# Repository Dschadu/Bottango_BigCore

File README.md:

# ESP32 Bottango Control Board

This custom PCB is designed to serve as a **control and interface board** for projects using the [Bottango](https://www.bottango.com/) motion and animation control firmware.  
It provides robust connectivity, servo control, and expandability for animatronics or motion-based systems.

**Note**: This is a community project and not designed / maintained / officially supported by Bottango.

---

## Features

### Core
- **ESP32 microcontroller**
- **USB-C** connector for power and programming  
- **Selectable power source** for the ESP32:  
  - USB-C  
  - 5 V rail (from WS2812B)

---

### Inputs
- **4 user buttons** — freely assignable, e.g., for selecting animations  
- **1 stop button** — emergency or animation stop  
- **Potentiometer input** — for audio volume control  

---

### Outputs & Indicators
- **4 status LEDs** — indicate board or animation states  
- **Line-out audio output**  
- **6 servo connectors** (powered by dedicated power input)  
- **WS2812B output** — supports addressable RGB LEDs  
- **Selectable power source for audio section:**  
  - USB-C  
  - 5 V rail (from WS2812B)  
- **LED power indicators** for:  
  - 5 V  
  - 6 V  
  - USB-C  
  - 3.3 V  

---

### Connectivity
- **I²C (Qwiic-compatible connector)** — for sensor or peripheral expansion  
- **RS485 interface** — for robust long-distance serial communication  

---

## Power Overview

| Function             | Voltage  | Source Options               |
|----------------------|----------|------------------------------|
| ESP32                | 5 V      | USB-C / 5 V line             |
| Audio Output Circuit | 5 V      | USB-C / 5 V line             |
| WS2812B LEDs         | 5 V      | External supply              |
| Servos               | 6 V      | External supply              |

---

## Firmware Compatibility

This board is designed for use with **Bottango firmware**, providing smooth integration with Bottango Studio for real-time motion and animation control.  
Learn more at: [https://www.bottango.com/](https://www.bottango.com/)

**Note**: This is a community project and not designed / maintained / officially supported by Bottango.

---

## License

This hardware design is released under the  
**CERN Open Hardware Licence Version 2 – Weakly Reciprocal (CERN-OHL-W)**.  
© 2025 Martin Klein 

You are free to:
- Use, study, modify, and manufacture this design  
- Distribute modified versions under the same license  
- Incorporate this board into larger, closed-source systems, **as long as modifications to this board itself remain open-source**

For more information, see the [LICENSE](./LICENSE) file or the full text at
[CERN-OHL-W](https://gitlab.com/ohwr/project/cernohl/-/wikis/uploads/82b567f43ce515395f7ddbfbad7a8806/cern_ohl_w_v2.txt)

## Copyright Notice

Copyright Martin Klein 2025.

This source describes Open Hardware and is licensed under the CERN-OHLW v2

You may redistribute and modify this PCB and make products
using it under the terms of the CERN-OHL-W v2 (https:/cern.ch/cern-ohl).
This PCB is distributed WITHOUT ANY EXPRESS OR IMPLIED
WARRANTY, INCLUDING OF MERCHANTABILITY, SATISFACTORY QUALITY
AND FITNESS FOR A PARTICULAR PURPOSE. Please see the CERN-OHL-W v2
for applicable conditions.

Source location: https://github.com/Dschadu/Geistwerk-BigCore

As per CERN-OHL-W v2 section 4.1, should You produce hardware based on
these sources, You must maintain the Source Location visible in its
documentation.

## Acknowledgments

Special thanks to the Bottango team for providing an intuitive open platform for animatronic motion control.

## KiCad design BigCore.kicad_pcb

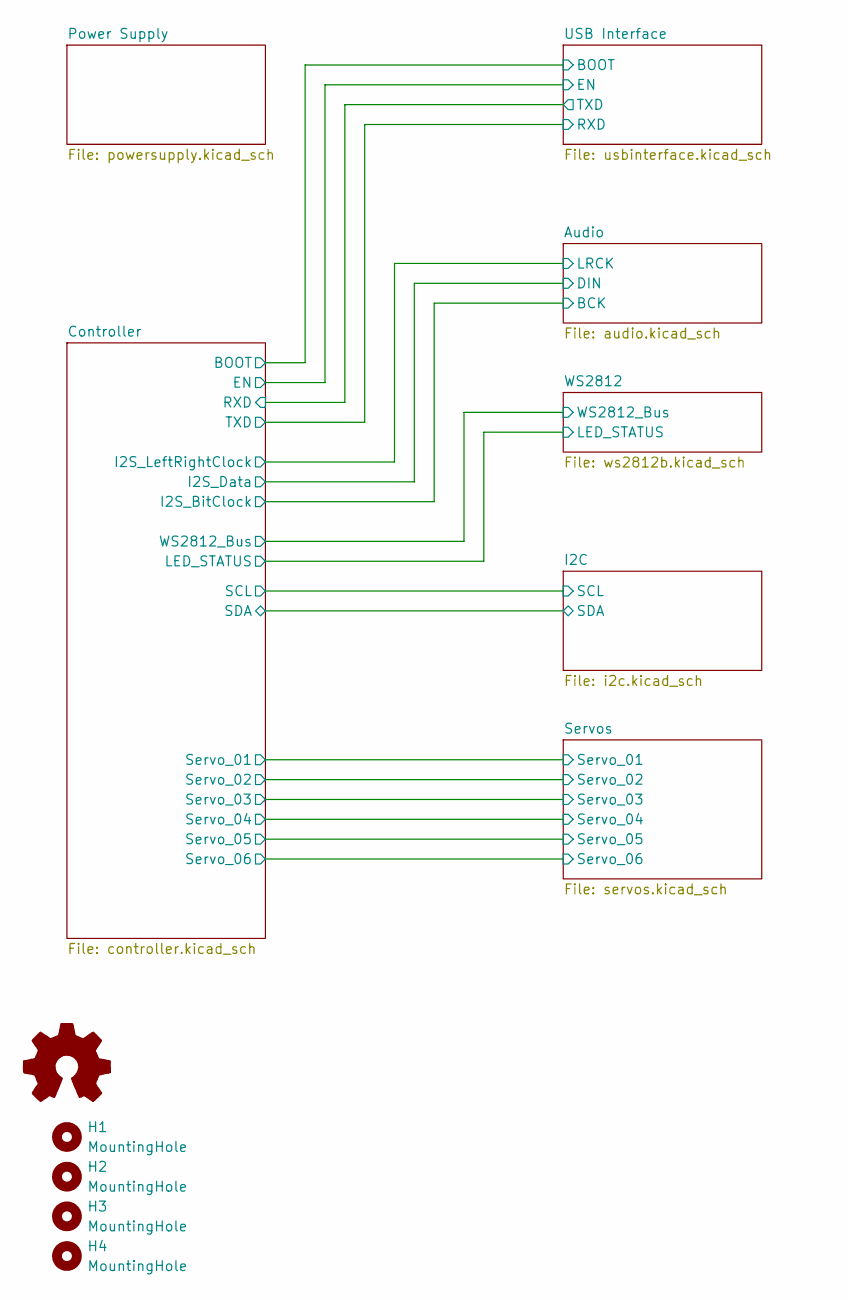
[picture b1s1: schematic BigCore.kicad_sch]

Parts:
H1, H2, H3, H4: MountingHole; MountingHole_3.2mm_M3
H5: Logo_Open_Hardware_Small; OSHW-Logo_5.7x6mm_SilkScreen

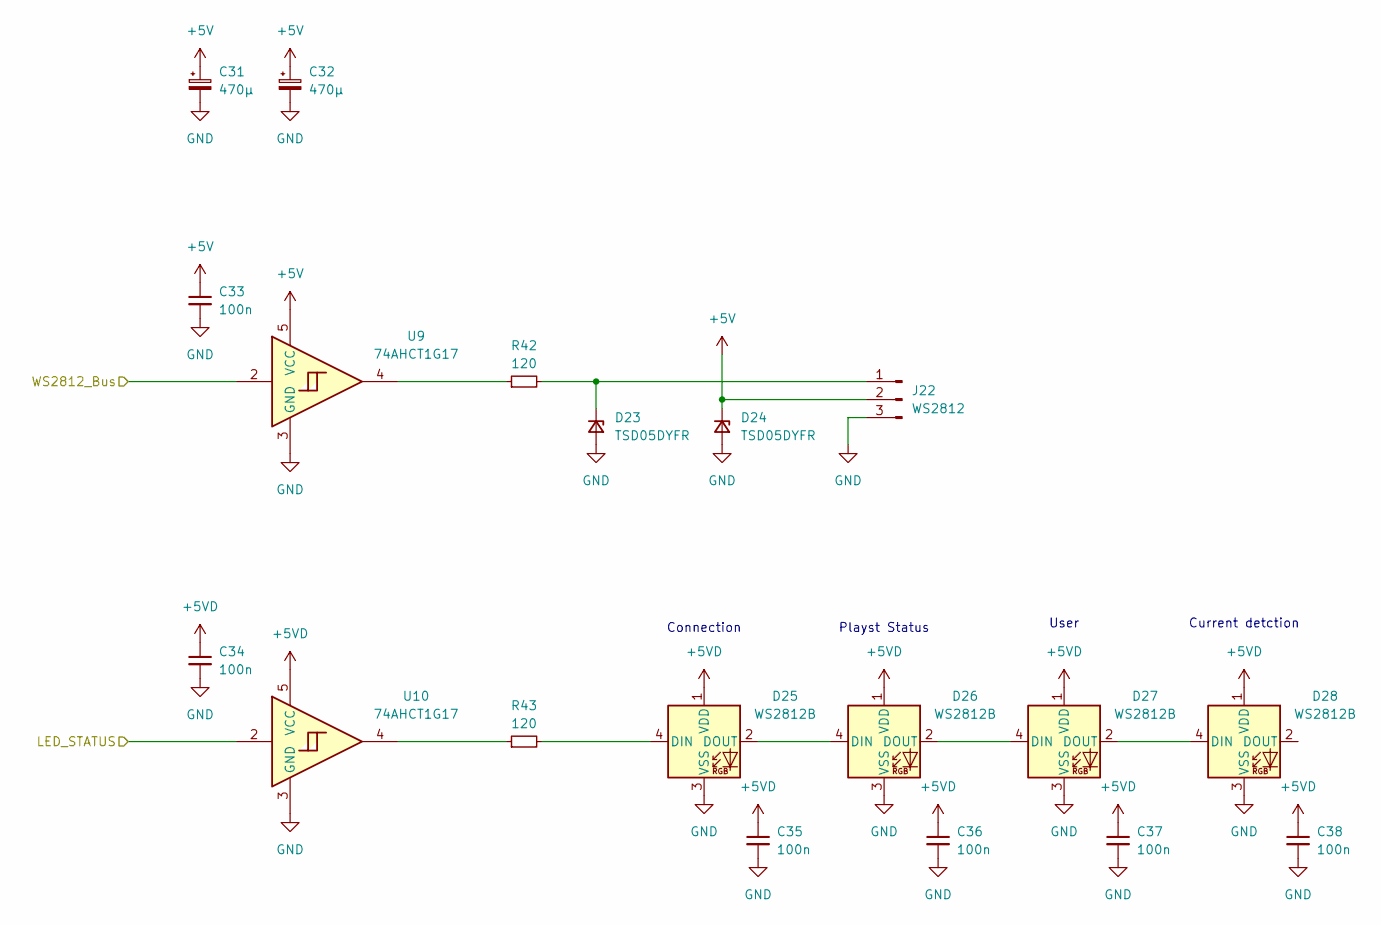
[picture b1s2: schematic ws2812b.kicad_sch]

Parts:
C31, C32: 470µ; CP_Radial_D8.0mm_P3.50mm
C33, C34, C35, C36, C37, C38: 100n; C_0603_1608Metric
D23, D24: TSD05DYFR; D_SOD-323_HandSoldering
D25, D26, D27, D28: WS2812B; LED_WS2812B-2020_PLCC4_2.0x2.0mm
J22: WS2812; JST_XH_B3B-XH-A_1x03_P2.50mm_Vertical
R42, R43: 120; R_0603_1608Metric
U9, U10: 74AHCT1G17; SOT-353_SC-70-5

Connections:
+5V: C31.1, C32.1, C33.1, D24.1 (K), J22.2, U9.5 (VCC); also elsewhere on the board
+5VD: C34.1, C35.1, C36.1, C37.1, C38.1, D25.1 (VDD), D26.1 (VDD), D27.1 (VDD), D28.1 (VDD), U10.5 (VCC); also elsewhere on the board
/Controller/LED_STATUS: U10.2; also elsewhere on the board
/Controller/WS2812_Bus: U9.2; also elsewhere on the board
GND: C31.2, C32.2, C33.2, C34.2, C35.2, C36.2, C37.2, C38.2, D23.2 (A), D24.2 (A), D25.3 (VSS), D26.3 (VSS), D27.3 (VSS), D28.3 (VSS), J22.3, U9.3 (GND), U10.3 (GND); also elsewhere on the board
unnamed: D23.1 (K), J22.1, R42.2
unnamed: D25.4 (DIN), R43.2
unnamed: D25.2 (DOUT), D26.4 (DIN)
unnamed: D26.2 (DOUT), D27.4 (DIN)
unnamed: D27.2 (DOUT), D28.4 (DIN)
unnamed: R42.1, U9.4
unnamed: R43.1, U10.4

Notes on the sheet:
Current detction
User
Connection
Playst Status

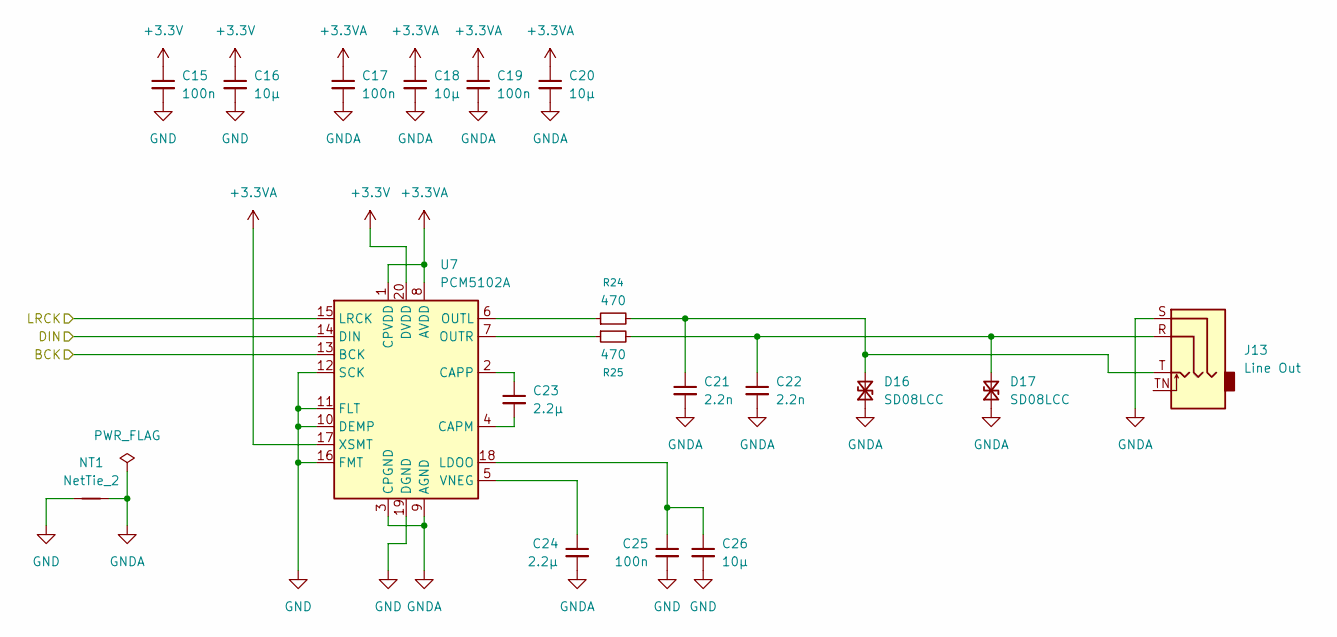
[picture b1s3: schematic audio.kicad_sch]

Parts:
C15, C17, C19, C25: 100n; C_0603_1608Metric
C16, C18, C20, C26: 10µ; C_0603_1608Metric
C21, C22: 2.2n; C_0603_1608Metric
C23, C24: 2.2µ; C_0603_1608Metric
D16, D17: SD08LCC; D_SOD-323_HandSoldering
J13: Line Out; Jack_3.5mm_CUI_SJ1-3524N_Horizontal
NT1: NetTie_2; NetTie-2_SMD_Pad0.5mm
R24, R25: 470; R_0603_1608Metric
U7: PCM5102A; TSSOP-20_4.4x6.5mm_P0.65mm

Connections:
+3.3V: C15.1, C16.1, U7.20 (DVDD); also elsewhere on the board
+3.3VA: C17.1, C18.1, C19.1, C20.1, U7.1 (CPVDD), U7.8 (AVDD), U7.17 (XSMT); also elsewhere on the board
/Controller/I2S_BitClock: U7.13 (BCK); also elsewhere on the board
/Controller/I2S_Data: U7.14 (DIN); also elsewhere on the board
/Controller/I2S_LeftRightClock: U7.15 (LRCK); also elsewhere on the board
GND: C15.2, C16.2, C25.2, C26.2, NT1.1, U7.10 (DEMP), U7.11 (FLT), U7.12 (SCK), U7.16 (FMT), U7.19 (DGND); also elsewhere on the board
GNDA: C17.2, C18.2, C19.2, C20.2, C21.2, C22.2, C24.2, D16.1 (A1), D17.1 (A1), J13.S, NT1.2, U7.3 (CPGND), U7.9 (AGND); also elsewhere on the board
unnamed: C21.1, D16.2 (A2), J13.T, R24.2
unnamed: C22.1, D17.2 (A2), J13.R, R25.2
unnamed: C23.2, U7.4 (CAPM)
unnamed: C23.1, U7.2 (CAPP)
unnamed: C25.1, C26.1, U7.18 (LDOO)
unnamed: R24.1, U7.6 (OUTL)
unnamed: R25.1, U7.7 (OUTR)
unnamed: C24.1, U7.5 (VNEG)

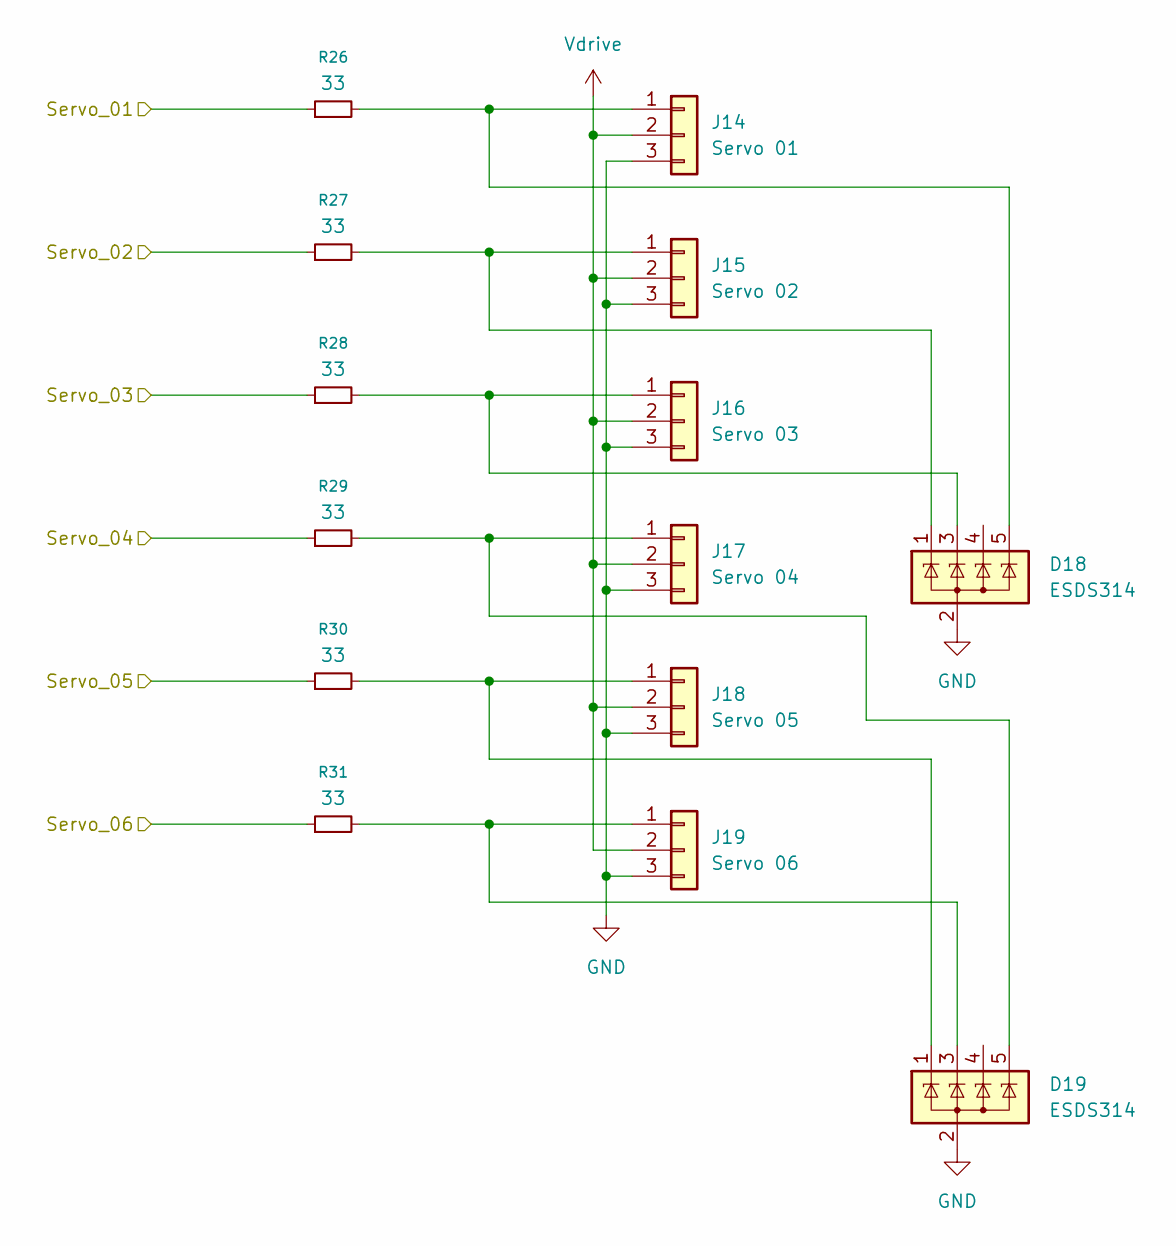
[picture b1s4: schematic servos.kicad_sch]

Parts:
D18, D19: ESDS314; SOT-23-5
J14: Servo 01; PinHeader_1x03_P2.54mm_Vertical
J15: Servo 02; PinHeader_1x03_P2.54mm_Vertical
J16: Servo 03; PinHeader_1x03_P2.54mm_Vertical
J17: Servo 04; PinHeader_1x03_P2.54mm_Vertical
J18: Servo 05; PinHeader_1x03_P2.54mm_Vertical
J19: Servo 06; PinHeader_1x03_P2.54mm_Vertical
R26, R27, R28, R29, R30, R31: 33; R_0603_1608Metric

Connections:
/Controller/Servo_01: R26.1; also elsewhere on the board
/Controller/Servo_02: R27.1; also elsewhere on the board
/Controller/Servo_03: R28.1; also elsewhere on the board
/Controller/Servo_04: R29.1; also elsewhere on the board
/Controller/Servo_05: R30.1; also elsewhere on the board
/Controller/Servo_06: R31.1; also elsewhere on the board
GND: D18.2 (A), D19.2 (A), J14.3, J15.3, J16.3, J17.3, J18.3, J19.3; also elsewhere on the board
unnamed: D18.5 (K), J14.1, R26.2
unnamed: D18.1 (K), J15.1, R27.2
unnamed: D18.3 (K), J16.1, R28.2
unnamed: D19.5 (K), J17.1, R29.2
unnamed: D19.1 (K), J18.1, R30.2
unnamed: D19.3 (K), J19.1, R31.2
Vdrive: J14.2, J15.2, J16.2, J17.2, J18.2, J19.2; also elsewhere on the board

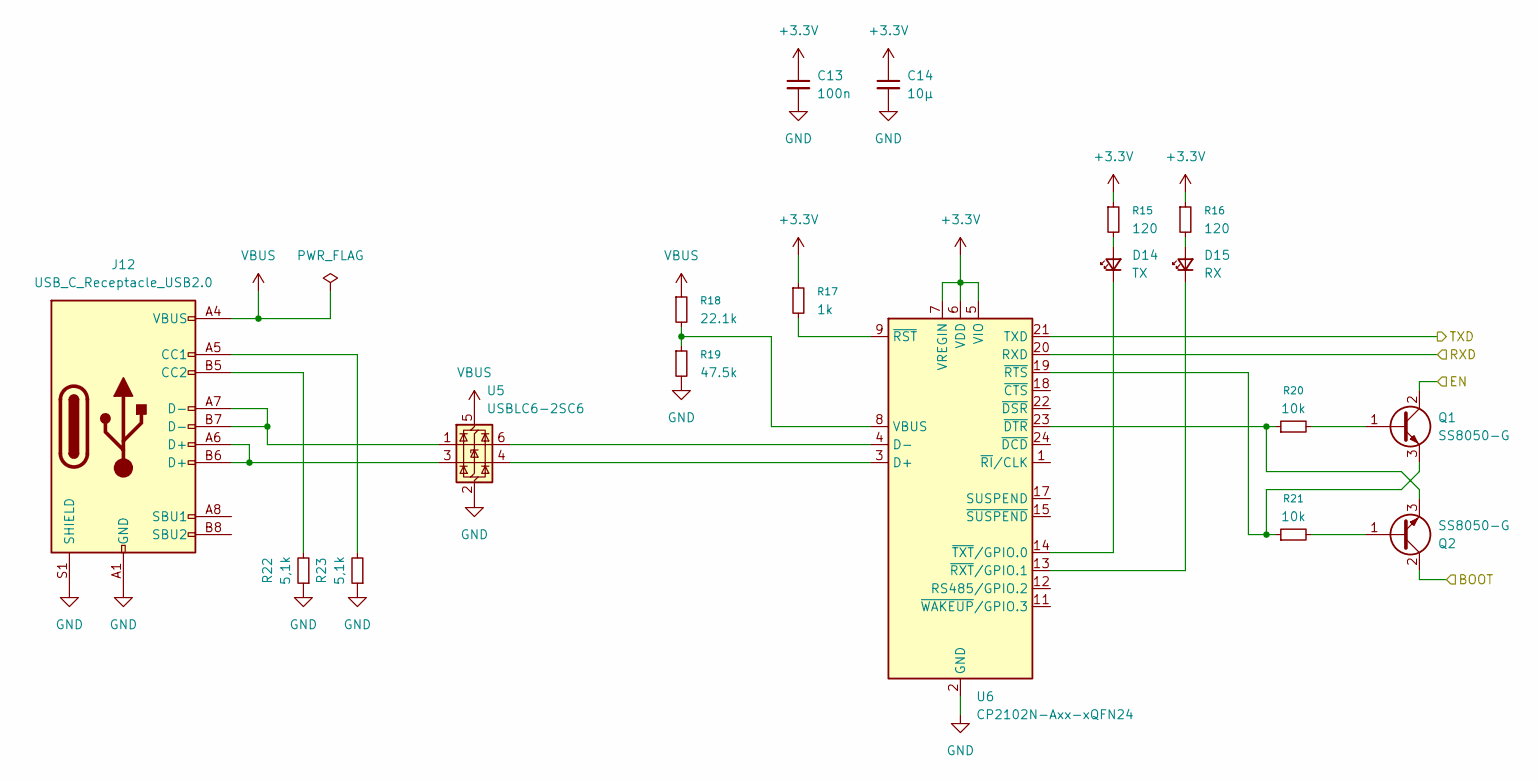
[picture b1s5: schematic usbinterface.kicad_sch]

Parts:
C13: 100n; C_0603_1608Metric
C14: 10µ; C_0603_1608Metric
D14: TX; LED_0805_2012Metric
D15: RX; LED_0805_2012Metric
J12: USB_C_Receptacle_USB2.0; USB_C_Receptacle_GCT_USB4105-xx-A_16P_TopMnt_Horizontal
Q1, Q2: SS8050-G; SOT-23-3
R15, R16: 120; R_0603_1608Metric
R17: 1k; R_0603_1608Metric
R18: 22.1k; R_0603_1608Metric
R19: 47.5k; R_0603_1608Metric
R20, R21: 10k; R_0603_1608Metric
R22, R23: 5,1k; R_0603_1608Metric
U5: USBLC6-2SC6; SOT-23-6
U6: CP2102N-Axx-xQFN24; QFN-24-1EP_4x4mm_P0.5mm_EP2.6x2.6mm

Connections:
+3.3V: C13.1, C14.1, R15.1, R16.1, R17.1, U6.5 (VIO), U6.6 (VDD), U6.7 (VREGIN); also elsewhere on the board
/Controller/BOOT: Q2.2 (C); also elsewhere on the board
/Controller/EN: Q1.2 (C); also elsewhere on the board
/Controller/RXD: U6.21 (TXD); also elsewhere on the board
/Controller/TXD: U6.20 (RXD); also elsewhere on the board
GND: C13.2, C14.2, J12.A1 (GND), J12.A12 (GND), J12.B1 (GND), J12.B12 (GND), J12.S1 (SHIELD), R19.2, R22.1, R23.1, U5.2 (GND), U6.2 (GND), U6.25 (GND); also elsewhere on the board
unnamed: D14.2 (A), R15.2
unnamed: D14.1 (K), U6.14 (~TXT/GPIO.0)
unnamed: D15.2 (A), R16.2
unnamed: D15.1 (K), U6.13 (~RXT/GPIO.1)
unnamed: J12.A5 (CC1), R23.2
unnamed: J12.B5 (CC2), R22.2
unnamed: J12.A6 (D+), J12.B6 (D+), U5.3 (I/O2)
unnamed: J12.A7 (D-), J12.B7 (D-), U5.1 (I/O1)
unnamed: Q1.1 (B), R20.2
unnamed: Q1.3 (E), R21.1, U6.19 (~RTS)
unnamed: Q2.1 (B), R21.2
unnamed: Q2.3 (E), R20.1, U6.23 (~DTR)
unnamed: U5.4 (I/O2), U6.3 (D+)
unnamed: U5.6 (I/O1), U6.4 (D-)
unnamed: R18.2, R19.1, U6.8 (VBUS)
unnamed: R17.2, U6.9 (~RST)
VBUS: J12.A4 (VBUS), J12.A9 (VBUS), J12.B4 (VBUS), J12.B9 (VBUS), R18.1, U5.5 (VBUS); also elsewhere on the board

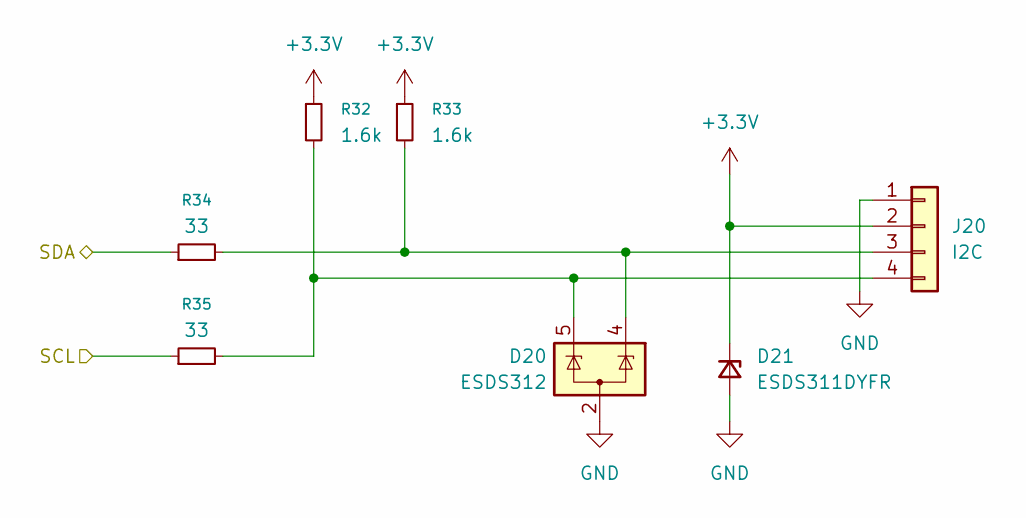
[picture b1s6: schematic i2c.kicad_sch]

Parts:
D20: ESDS312; SOT-23-5
D21: ESDS311DYFR; D_SOD-323_HandSoldering
J20: I2C; JST_SH_SM04B-SRSS-TB_1x04-1MP_P1.00mm_Horizontal
R32, R33: 1.6k; R_0603_1608Metric
R34, R35: 33; R_0603_1608Metric

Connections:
+3.3V: D21.1 (K), J20.2, R32.1, R33.1; also elsewhere on the board
/Controller/SCL: R35.1; also elsewhere on the board
/Controller/SDA: R34.1; also elsewhere on the board
GND: D20.2 (A), D21.2 (A), J20.1; also elsewhere on the board
unnamed: D20.4 (K), J20.3, R33.2, R34.2
unnamed: D20.5 (K), J20.4, R32.2, R35.2

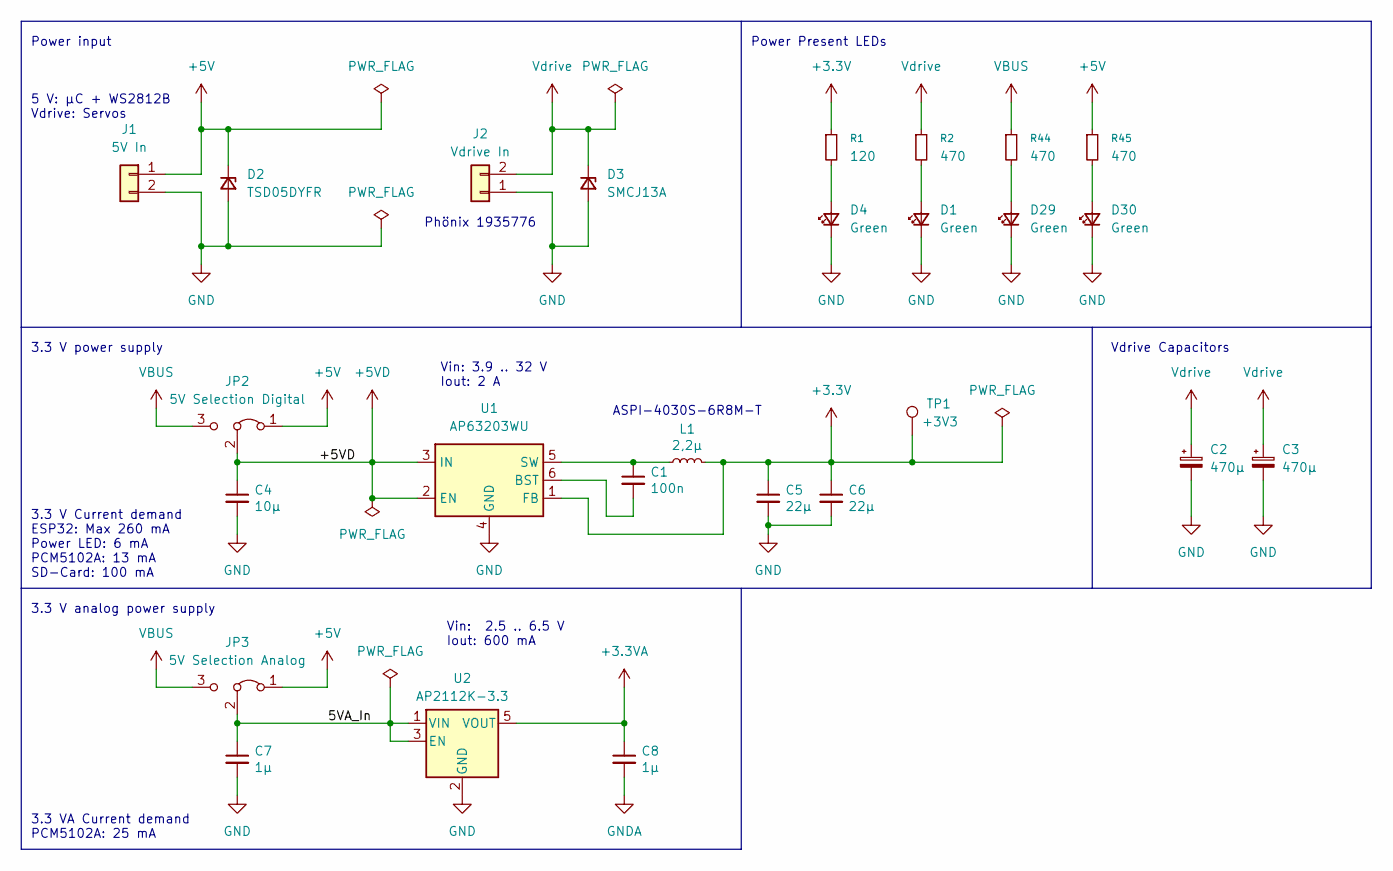
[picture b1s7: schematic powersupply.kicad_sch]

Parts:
C1: 100n; C_0603_1608Metric
C2, C3: 470µ; CP_Radial_D8.0mm_P3.50mm
C4: 10µ; C_0603_1608Metric
C5, C6: 22µ; C_0805_2012Metric
C7, C8: 1µ; C_0603_1608Metric
D1, D4, D29, D30: Green; LED_0805_2012Metric
D2: TSD05DYFR; D_SOD-323_HandSoldering
D3: SMCJ13A; D_SMA_Handsoldering
J1: 5V In; JST_XH_B2B-XH-A_1x02_P2.50mm_Vertical
J2: Vdrive In; TerminalBlock_Phoenix_PT-1,5-2-5.0-H_1x02_P5.00mm_Horizontal
JP2: 5V Selection Digital; PinHeader_1x03_P2.54mm_Vertical
JP3: 5V Selection Analog; PinHeader_1x03_P2.54mm_Vertical
L1: 2,2µ; L_APV_ANR4020
R1: 120; R_0603_1608Metric
R2, R44, R45: 470; R_0603_1608Metric
TP1: +3V3; TestPoint_Pad_D1.5mm
U1: AP63203WU; TSOT-23-6
U2: AP2112K-3.3; SOT-23-5

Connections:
+3.3V: C5.1, C6.1, L1.2, R1.1, TP1.1, U1.1 (FB); also elsewhere on the board
+3.3VA: C8.1, U2.5 (VOUT); also elsewhere on the board
+5V: D2.1 (K), J1.1, JP2.1 (A), JP3.1 (A), R45.1; also elsewhere on the board
+5VD: C4.1, JP2.2 (C), U1.2 (EN), U1.3 (IN); also elsewhere on the board
/Power Supply/5VA_In: C7.1, JP3.2 (C), U2.1 (VIN), U2.3 (EN)
GND: C2.2, C3.2, C4.2, C5.2, C6.2, C7.2, D1.1 (K), D2.2 (A), D3.2 (A), D4.1 (K), D29.1 (K), D30.1 (K), J1.2, J2.1, U1.4 (GND), U2.2 (GND); also elsewhere on the board
GNDA: C8.2; also elsewhere on the board
unnamed: D1.2 (A), R2.2
unnamed: D4.2 (A), R1.2
unnamed: D29.2 (A), R44.2
unnamed: D30.2 (A), R45.2
unnamed: C1.2, U1.6 (BST)
unnamed: C1.1, L1.1, U1.5 (SW)
VBUS: JP2.3 (B), JP3.3 (B), R44.1; also elsewhere on the board
Vdrive: C2.1, C3.1, D3.1 (K), J2.2, R2.1; also elsewhere on the board

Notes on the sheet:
Power Present LEDs
Vdrive Capacitors
Phönix 1935776
Power input
Vin: 2.5 .. 6.5 V Iout: 600 mA
ASPI-4030S-6R8M-T
3.3 V Current demand ESP32: Max 260 mA Power LED: 6 mA PCM5102A: 13 mA SD-Card: 100 mA
5 V: µC + WS2812B Vdrive: Servos
3.3 V power supply
Vin: 3.9 .. 32 V Iout: 2 A
3.3 VA Current demand PCM5102A: 25 mA
3.3 V analog power supply

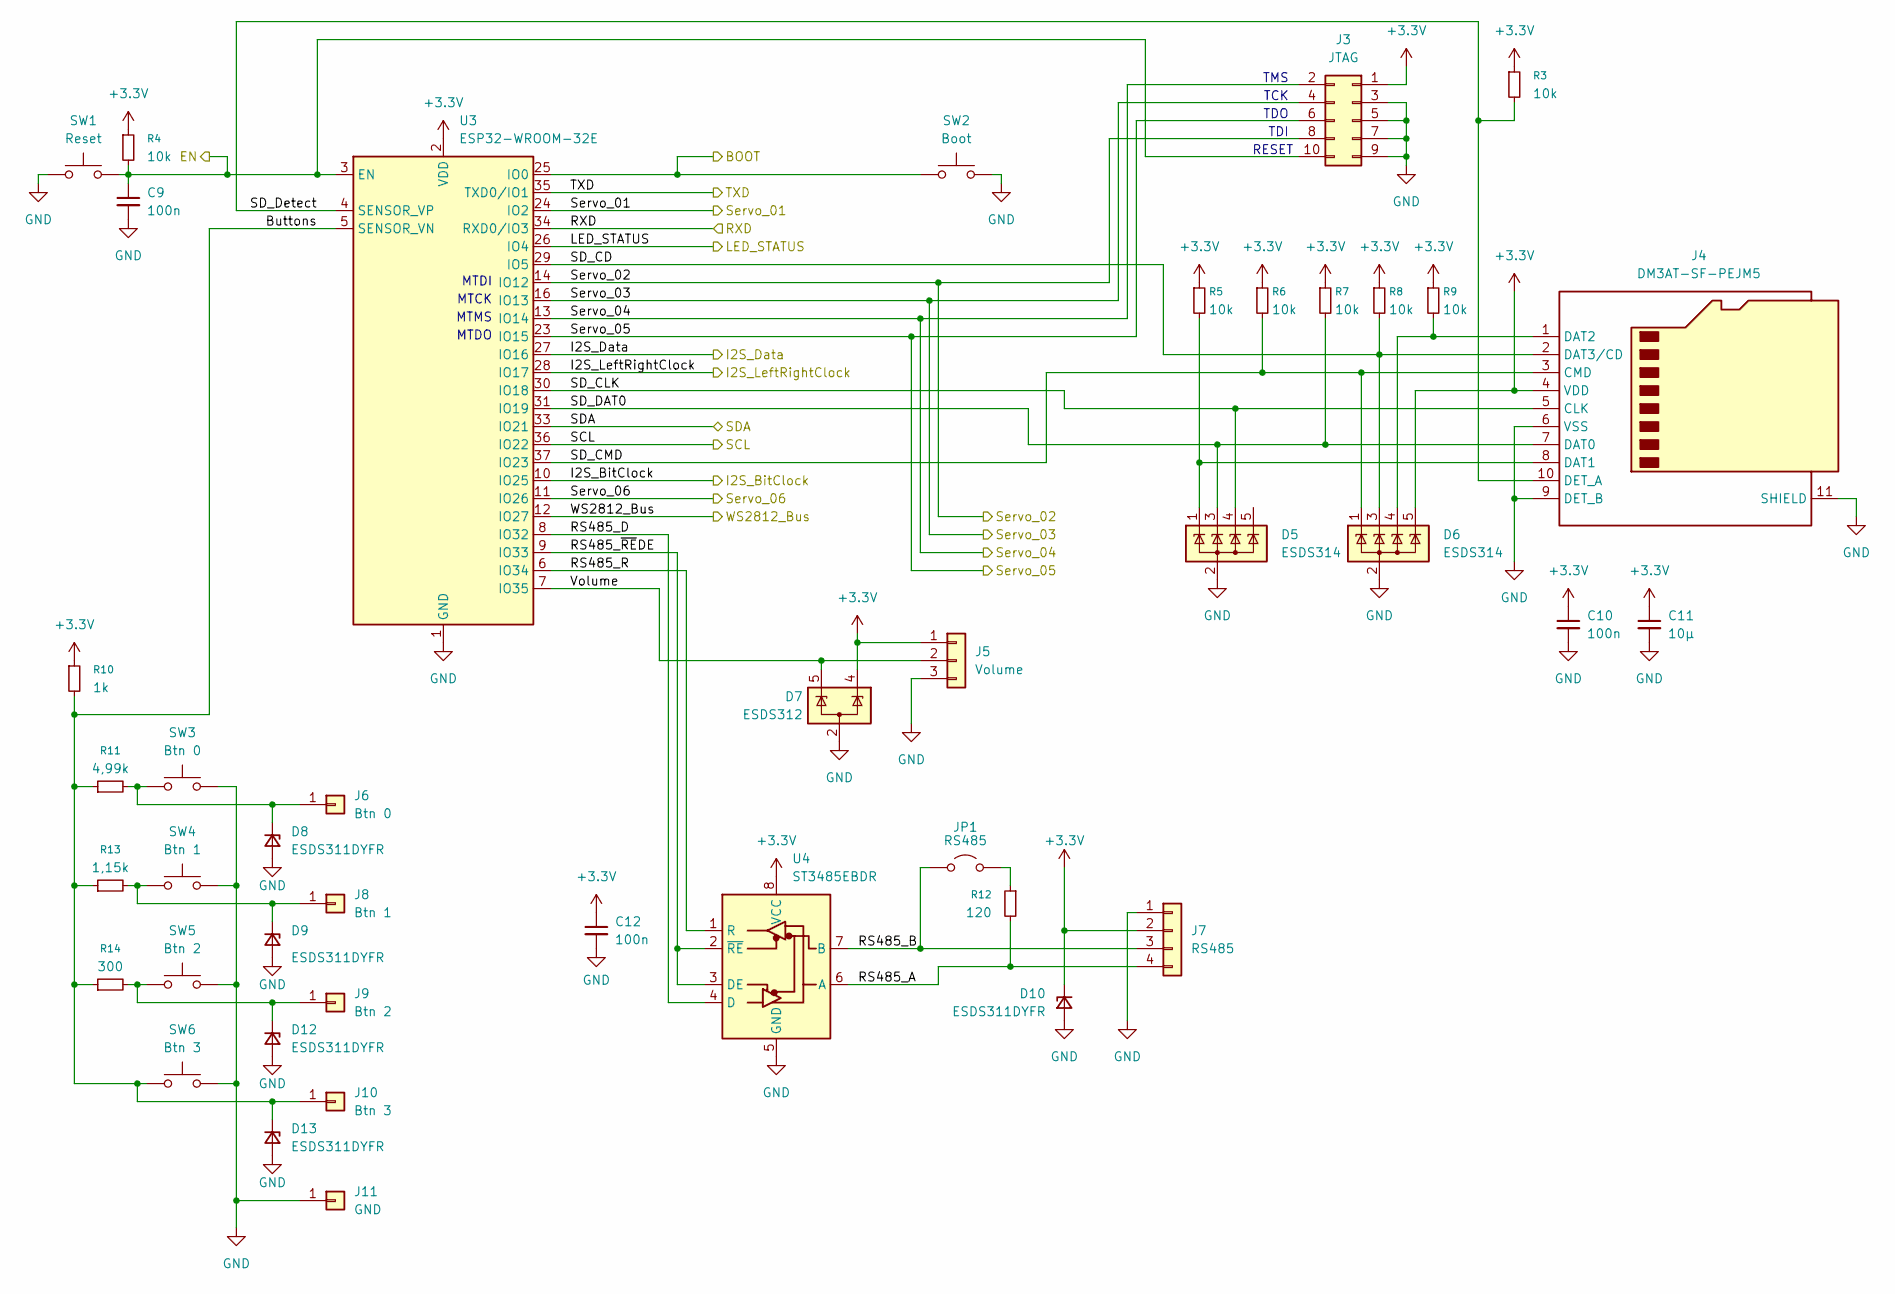
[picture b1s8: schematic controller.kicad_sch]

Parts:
C9, C10, C12: 100n; C_0603_1608Metric
C11: 10µ; C_0603_1608Metric
D5, D6: ESDS314; SOT-23-5
D7: ESDS312; SOT-23-5
D8, D9, D10, D12, D13: ESDS311DYFR; D_SOD-323_HandSoldering
J3: JTAG; PinHeader_2x05_P1.27mm_Vertical
J4: DM3AT-SF-PEJM5; microSD_HC_Hirose_DM3AT-SF-PEJM5
J5: Volume; PinHeader_1x03_P2.54mm_Vertical
J6: Btn 0; TestPoint_Pad_D1.5mm
J7: RS485; JST_SH_SM04B-SRSS-TB_1x04-1MP_P1.00mm_Horizontal
J8: Btn 1; TestPoint_Pad_D1.5mm
J9: Btn 2; TestPoint_Pad_D1.5mm
J10: Btn 3; TestPoint_Pad_D1.5mm
J11: GND; TestPoint_Pad_D2.0mm
JP1: RS485; PinHeader_1x02_P2.54mm_Vertical
R3, R4, R5, R6, R7, R8, R9: 10k; R_0603_1608Metric
R10: 1k; R_0603_1608Metric
R11: 4,99k; R_0603_1608Metric
R12: 120; R_0603_1608Metric
R13: 1,15k; R_0603_1608Metric
R14: 300; R_0603_1608Metric
SW1: Reset; SW_Push_1P1T_NO_CK_KSC7xxJ
SW2: Boot; SW_Push_1P1T_NO_CK_KSC7xxJ
SW3: Btn 0; SW_Push_1P1T_NO_CK_KSC7xxJ
SW4: Btn 1; SW_Push_1P1T_NO_CK_KSC7xxJ
SW5: Btn 2; SW_Push_1P1T_NO_CK_KSC7xxJ
SW6: Btn 3; SW_Push_1P1T_NO_CK_KSC7xxJ
U3: ESP32-WROOM-32E
U4: ST3485EBDR; SOIC-8_3.9x4.9mm_P1.27mm

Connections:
+3.3V: C10.1, C11.1, C12.1, D6.5 (K), D7.4 (K), D10.1 (K), J3.1, J4.4 (VDD), J5.1, J7.2, R3.1, R4.1, R5.1, R6.1, R7.1, R8.1, R9.1, R10.1, U3.2 (VDD), U4.8 (VCC); also elsewhere on the board
/Controller/BOOT: SW2.1, U3.25 (IO0); also elsewhere on the board
/Controller/Buttons: D13.1 (K), J10.1, R10.2, R11.1, R13.1, R14.1, SW6.2, U3.5 (SENSOR_VN)
/Controller/EN: C9.1, J3.10, R4.2, SW1.1, U3.3 (EN); also elsewhere on the board
/Controller/I2S_BitClock: U3.10 (IO25); also elsewhere on the board
/Controller/I2S_Data: U3.27 (IO16); also elsewhere on the board
/Controller/I2S_LeftRightClock: U3.28 (IO17); also elsewhere on the board
/Controller/LED_STATUS: U3.26 (IO4); also elsewhere on the board
/Controller/RS485_A: J7.4, R12.2, U4.6 (A)
/Controller/RS485_B: J7.3, JP1.1 (A), U4.7 (B)
/Controller/RS485_D: U3.8 (IO32), U4.4 (D)
/Controller/RS485_R: U3.6 (IO34), U4.1 (R)
/Controller/RS485_~REDE: U3.9 (IO33), U4.2 (~RE), U4.3 (DE)
/Controller/RXD: U3.34 (RXD0/IO3); also elsewhere on the board
/Controller/SCL: U3.36 (IO22); also elsewhere on the board
/Controller/SDA: U3.33 (IO21); also elsewhere on the board
/Controller/SD_CD: D6.3 (K), J4.2 (DAT3/CD), R8.2, U3.29 (IO5)
/Controller/SD_CLK: D5.4 (K), J4.5 (CLK), U3.30 (IO18)
/Controller/SD_CMD: D6.1 (K), J4.3 (CMD), R6.2, U3.37 (IO23)
/Controller/SD_DAT0: D5.3 (K), J4.7 (DAT0), R7.2, U3.31 (IO19)
/Controller/SD_Detect: J4.10 (DET_A), R3.2, U3.4 (SENSOR_VP)
/Controller/Servo_01: U3.24 (IO2); also elsewhere on the board
/Controller/Servo_02: J3.8, U3.14 (IO12); also elsewhere on the board
/Controller/Servo_03: J3.4, U3.16 (IO13); also elsewhere on the board
/Controller/Servo_04: J3.2, U3.13 (IO14); also elsewhere on the board
/Controller/Servo_05: J3.6, U3.23 (IO15); also elsewhere on the board
/Controller/Servo_06: U3.11 (IO26); also elsewhere on the board
/Controller/TXD: U3.35 (TXD0/IO1); also elsewhere on the board
/Controller/Volume: D7.5 (K), J5.2, U3.7 (IO35)
/Controller/WS2812_Bus: U3.12 (IO27); also elsewhere on the board
GND: C9.2, C10.2, C11.2, C12.2, D5.2 (A), D6.2 (A), D7.2 (A), D8.2 (A), D9.2 (A), D10.2 (A), D12.2 (A), D13.2 (A), J3.3, J3.5, J3.7, J3.9, J4.6 (VSS), J4.9 (DET_B), J4.11 (SHIELD), J5.3, J7.1, J11.1, SW1.2, SW2.2, SW3.1, SW4.1, SW5.1, SW6.1, U3.1 (GND), U3.15 (GND), U3.38 (GND), U3.39 (GND), U4.5 (GND); also elsewhere on the board
unnamed: D8.1 (K), J6.1, R11.2, SW3.2
unnamed: D9.1 (K), J8.1, R13.2, SW4.2
unnamed: D12.1 (K), J9.1, R14.2, SW5.2
unnamed: D5.1 (K), J4.8 (DAT1), R5.2
unnamed: D6.4 (K), J4.1 (DAT2), R9.2
unnamed: JP1.2 (B), R12.1

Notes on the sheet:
MTDO
MTCK
RESET
TMS
MTDI
MTMS
TCK
TDO
TDI

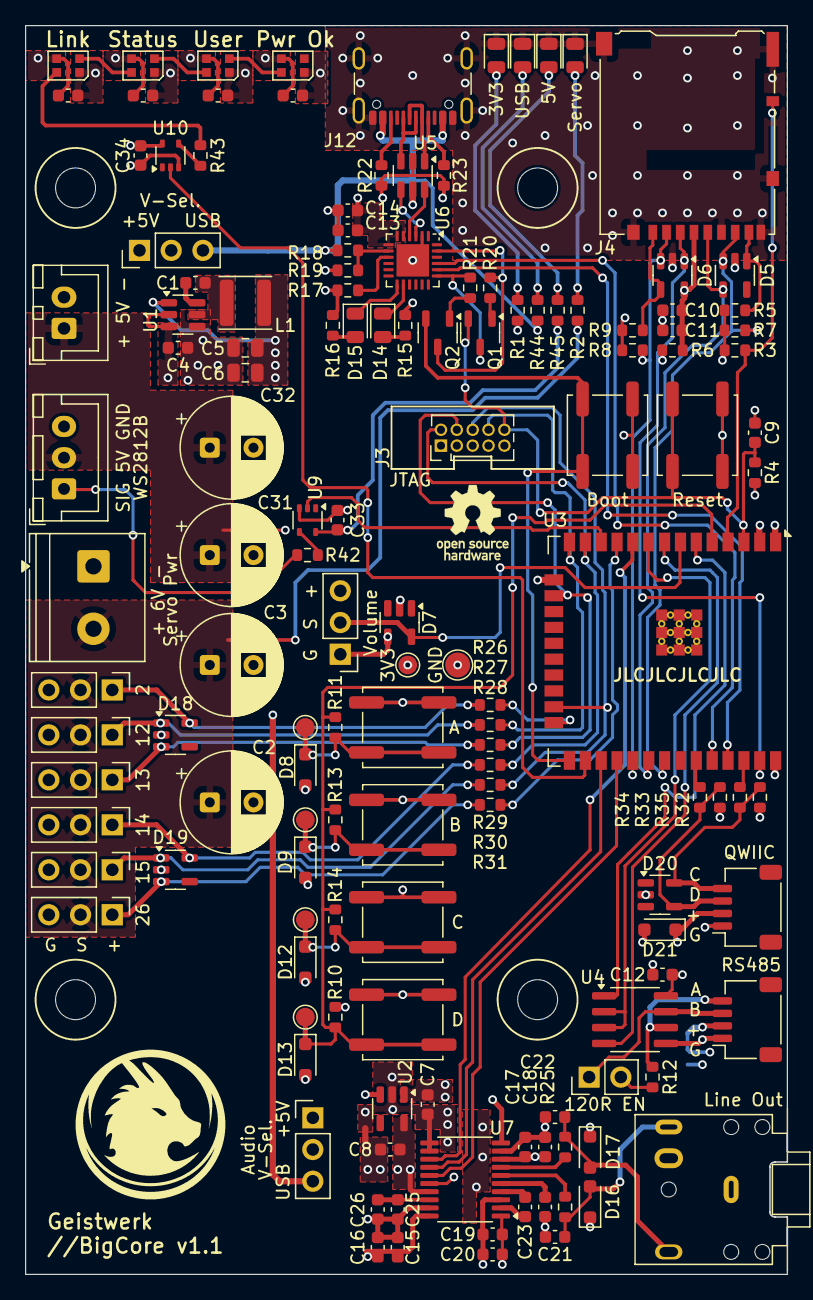
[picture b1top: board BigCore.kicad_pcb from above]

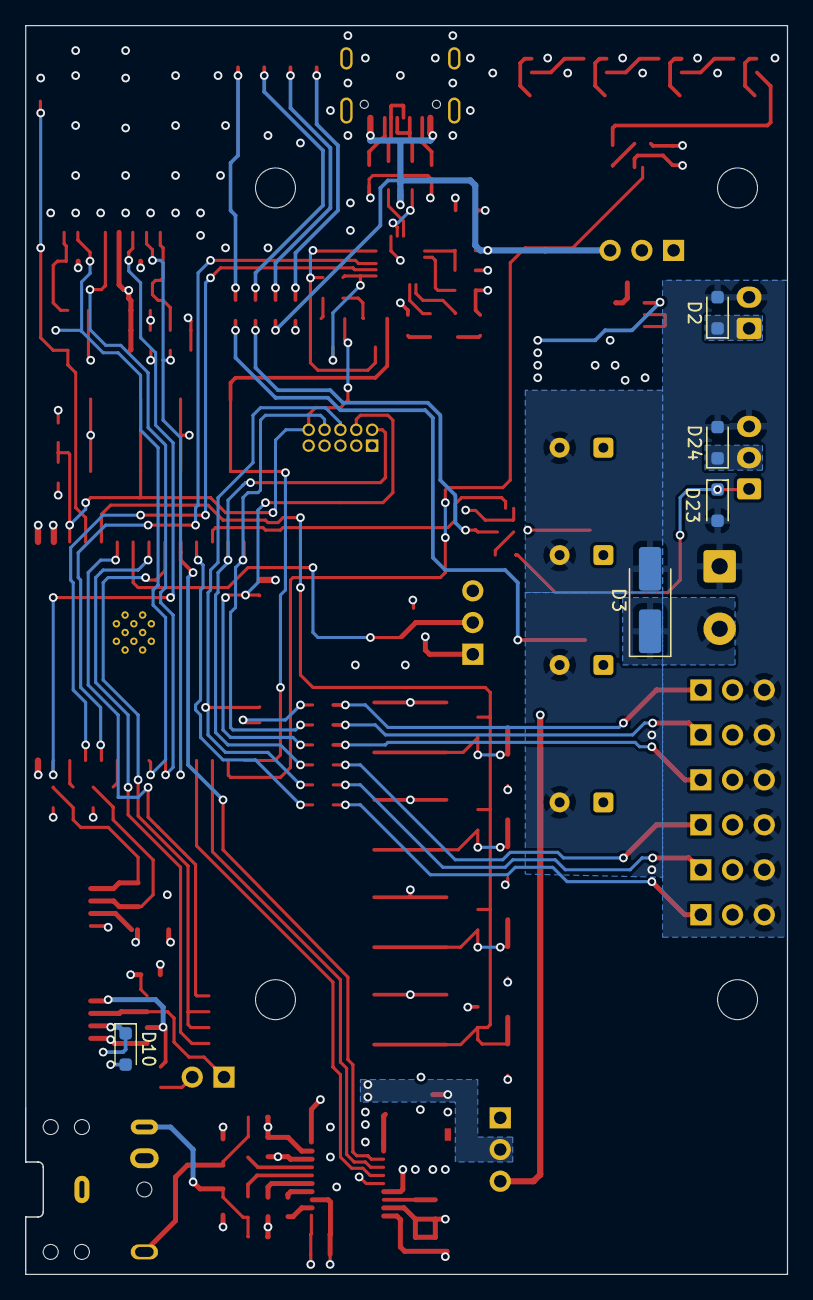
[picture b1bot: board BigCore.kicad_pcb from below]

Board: 4 copper layers, 61.0 x 100.0 mm, 150 parts (5 on the bottom side), 89 nets.

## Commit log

2025-09-04 Changed .gitignore
2025-09-04 - I2C entfernt - Logo hinzugefügt - Spannungsauswahl für Audio (USB oder +5V) hinzugefügt - Spannung für WS2812 LEDs ändert sich jetzt zusammen mit +5VD Auswahl
2025-09-05 Changed the WS2812 driver IC Optimized the Analog GND and AVCC routing Changed RS485 driver Removed TVS Diode at the RS485 driver (already has 15kV rating)
2025-09-08 Changed Line Out Connector
    Changed Line Out Connector
2025-09-13 Footprint changes
    Changed WS2812 from 5050 to 2020
    Changed ESP32 to correct revision
2025-09-14 First Manufactured Version
    A few silkscreen changes
2025-09-27 SD-Card Fix
    - DAT0 and DAT1 where flipped
    - Changed footprint for ESD-Diodes D16 and D17 to be more hand-soldering friendly
2025-09-27 Silkscreen fix
    Fixed wrong silkcreen text for the DAC Voltage-Source. USB and +5V are flipped
2025-10-05 PCB Version Bump
    -Bumped PCB to Version 1.1
2025-10-05 Added Licence and Readme
2025-10-05 Added schematic as pdf
2025-10-05 Changed README
2025-10-06 Renamed PCB
2025-10-06 Added License
2025-10-11 Refreshed the BOM
